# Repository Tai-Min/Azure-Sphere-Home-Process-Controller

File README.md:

# Azure Sphere Home Process Controller
My entry for [Home Is Where the Hack Is Challenge, with Avnet Azure Sphere](https://www.element14.com/community/docs/DOC-94716?CMP=e-email-ADH-e14-Com-170420-Avnet-2391) (Grand Prize winner!)

Industrial like PID / Two state process controller with web based configuration, MQTT communication and Azure IoT Central integration.

This repository contains source code for both High level application and real time core of Azure Sphere board, source codes for Arduino expansion cards, electronic design files for KiCad, housing design files for Autodesk Inventor and STL files for 3d printing.

For details how it was created and how to use it click [here](https://www.element14.com/community/groups/azuresphere/blog/2020/05/29/azure-sphere-home-process-controller)

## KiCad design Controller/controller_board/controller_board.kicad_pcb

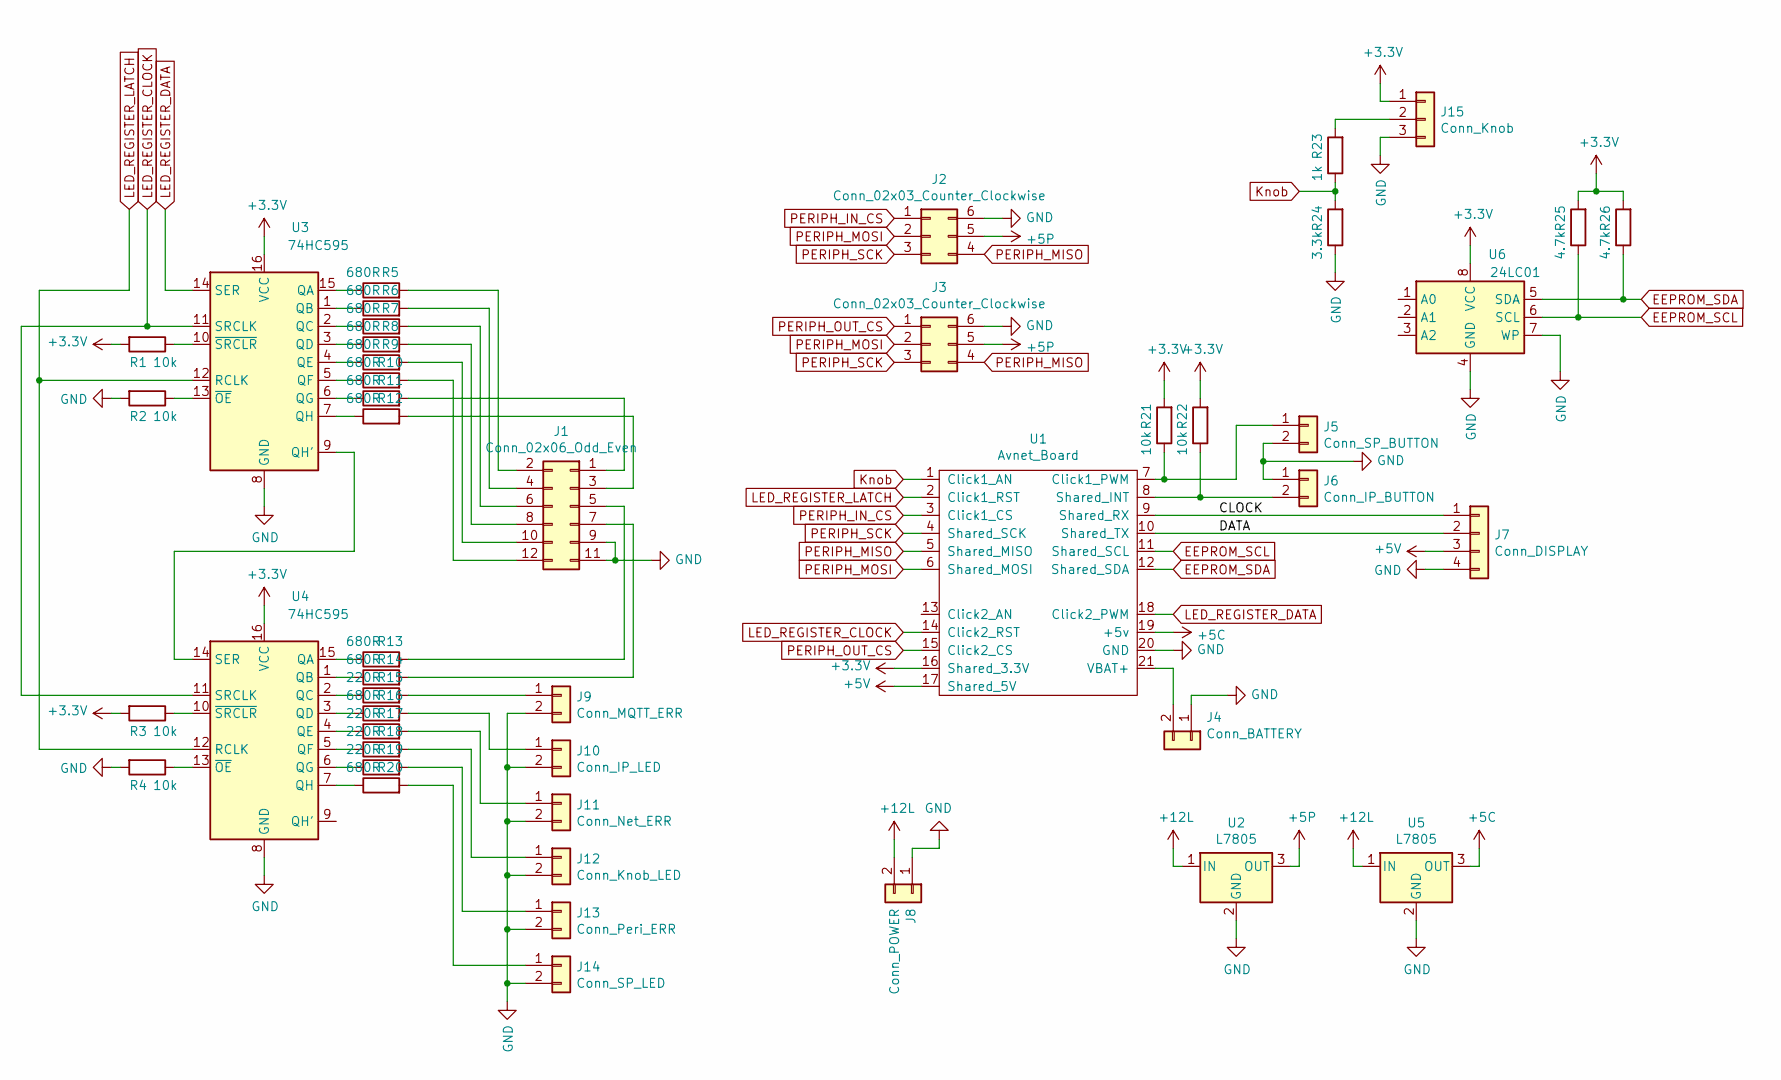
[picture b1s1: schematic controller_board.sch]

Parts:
J1: Conn_02x06_Odd_Even; PinHeader_2x06_P2.54mm_Vertical
J2: Conn_02x03_Counter_Clockwise; PinSocket_2x03_P2.54mm_Horizontal
J3: Conn_02x03_Counter_Clockwise; PinHeader_2x03_P2.54mm_Horizontal
J4: Conn_BATTERY; PinHeader_1x02_P2.54mm_Vertical
J5: Conn_SP_BUTTON; PinHeader_1x02_P2.54mm_Vertical
J6: Conn_IP_BUTTON; PinHeader_1x02_P2.54mm_Vertical
J7: Conn_DISPLAY; PinHeader_1x04_P2.54mm_Vertical
J8: Conn_POWER; PhoenixContact_MSTBA_2,5_2-G_1x02_P5.00mm_Horizontal
J9: Conn_MQTT_ERR; PinHeader_1x02_P2.54mm_Vertical
J10: Conn_IP_LED; PinHeader_1x02_P2.54mm_Vertical
J11: Conn_Net_ERR; PinHeader_1x02_P2.54mm_Vertical
J12: Conn_Knob_LED; PinHeader_1x02_P2.54mm_Vertical
J13: Conn_Peri_ERR; PinHeader_1x02_P2.54mm_Vertical
J14: Conn_SP_LED; PinHeader_1x02_P2.54mm_Vertical
J15: Conn_Knob; PinHeader_1x03_P2.54mm_Vertical
R1, R2, R3, R4, R21, R22: 10k; R_Axial_DIN0207_L6.3mm_D2.5mm_P10.16mm_Horizontal
R5, R6, R7, R8, R9, R10, R11, R12, R13, R14, R16, R20: 680R; R_Axial_DIN0207_L6.3mm_D2.5mm_P10.16mm_Horizontal
R15, R17, R18, R19: 220R; R_Axial_DIN0207_L6.3mm_D2.5mm_P10.16mm_Horizontal
R23: 1k; R_Axial_DIN0207_L6.3mm_D2.5mm_P10.16mm_Horizontal
R24: 3.3k; R_Axial_DIN0207_L6.3mm_D2.5mm_P10.16mm_Horizontal
R25, R26: 4.7k; R_Axial_DIN0207_L6.3mm_D2.5mm_P10.16mm_Horizontal
U1: Avnet_Board; Avnet_Azure_Sphere
U2, U5: L7805; TO-220-3_Vertical
U3, U4: 74HC595; DIP-16_W7.62mm_LongPads
U6: 24LC01; DIP-8_W7.62mm_LongPads

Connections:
+3V3: J15.1, R1.2, R3.2, R21.2, R22.2, R25.2, R26.2, U1.16 (Shared_3.3V), U3.16 (VCC), U4.16 (VCC), U6.8 (VCC)
+5C: U1.19 (+5v), U5.3 (OUT)
+5P: J2.5, J3.5, U2.3 (OUT)
+5V: J7.3, U1.17 (Shared_5V)
+12L: J8.2, U2.1 (IN), U5.1 (IN)
/CLOCK: J7.1, U1.9 (Shared_RX)
/DATA: J7.2, U1.10 (Shared_TX)
EEPROM_SCL: R25.1, U1.11 (Shared_SCL), U6.6 (SCL)
EEPROM_SDA: R26.1, U1.12 (Shared_SDA), U6.5 (SDA)
GND: J1.9, J1.11, J2.6, J3.6, J4.1, J5.2, J6.1, J7.4, J8.1, J9.2, J10.2, J11.2, J12.2, J13.2, J14.2, J15.3, R2.2, R4.2, R24.1, U1.20 (GND), U2.2 (GND), U3.8 (GND), U4.8 (GND), U5.2 (GND), U6.4 (GND), U6.7 (WP)
Knob: R23.1, R24.2, U1.1 (Click1_AN)
LED_REGISTER_CLOCK: U1.14 (Click2_RST), U3.11 (SRCLK), U4.11 (SRCLK)
LED_REGISTER_DATA: U1.18 (Click2_PWM), U3.14 (SER)
LED_REGISTER_LATCH: U1.2 (Click1_RST), U3.12 (RCLK), U4.12 (RCLK)
unnamed: J1.1, R11.2
unnamed: J1.2, R5.2
unnamed: J1.3, R12.2
unnamed: J1.4, R6.2
unnamed: J1.5, R13.2
unnamed: J1.6, R7.2
unnamed: J1.7, R14.2
unnamed: J1.8, R8.2
unnamed: J1.10, R9.2
unnamed: J1.12, R10.2
unnamed: J4.2, U1.21 (VBAT+)
unnamed: J5.1, R21.1, U1.7 (Click1_PWM)
unnamed: J6.2, R22.1, U1.8 (Shared_INT)
unnamed: J9.1, R15.2
unnamed: J10.1, R16.2
unnamed: J11.1, R17.2
unnamed: J12.1, R18.2
unnamed: J13.1, R19.2
unnamed: J14.1, R20.2
unnamed: J15.2, R23.2
unnamed: R1.1, U3.10 (~SRCLR)
unnamed: R2.1, U3.13 (~OE)
unnamed: R3.1, U4.10 (~SRCLR)
unnamed: R4.1, U4.13 (~OE)
unnamed: R5.1, U3.15 (QA)
unnamed: R6.1, U3.1 (QB)
unnamed: R7.1, U3.2 (QC)
unnamed: R8.1, U3.3 (QD)
unnamed: R9.1, U3.4 (QE)
unnamed: R10.1, U3.5 (QF)
unnamed: R11.1, U3.6 (QG)
unnamed: R12.1, U3.7 (QH)
unnamed: R13.1, U4.15 (QA)
unnamed: R14.1, U4.1 (QB)
unnamed: R15.1, U4.2 (QC)
unnamed: R16.1, U4.3 (QD)
unnamed: R17.1, U4.4 (QE)
unnamed: R18.1, U4.5 (QF)
unnamed: R19.1, U4.6 (QG)
unnamed: R20.1, U4.7 (QH)
unnamed: U3.9 (QH'), U4.14 (SER)
PERIPH_IN_CS: J2.1, U1.3 (Click1_CS)
PERIPH_MISO: J2.4, J3.4, U1.5 (Shared_MISO)
PERIPH_MOSI: J2.2, J3.2, U1.6 (Shared_MOSI)
PERIPH_OUT_CS: J3.1, U1.15 (Click2_CS)
PERIPH_SCK: J2.3, J3.3, U1.4 (Shared_SCK)

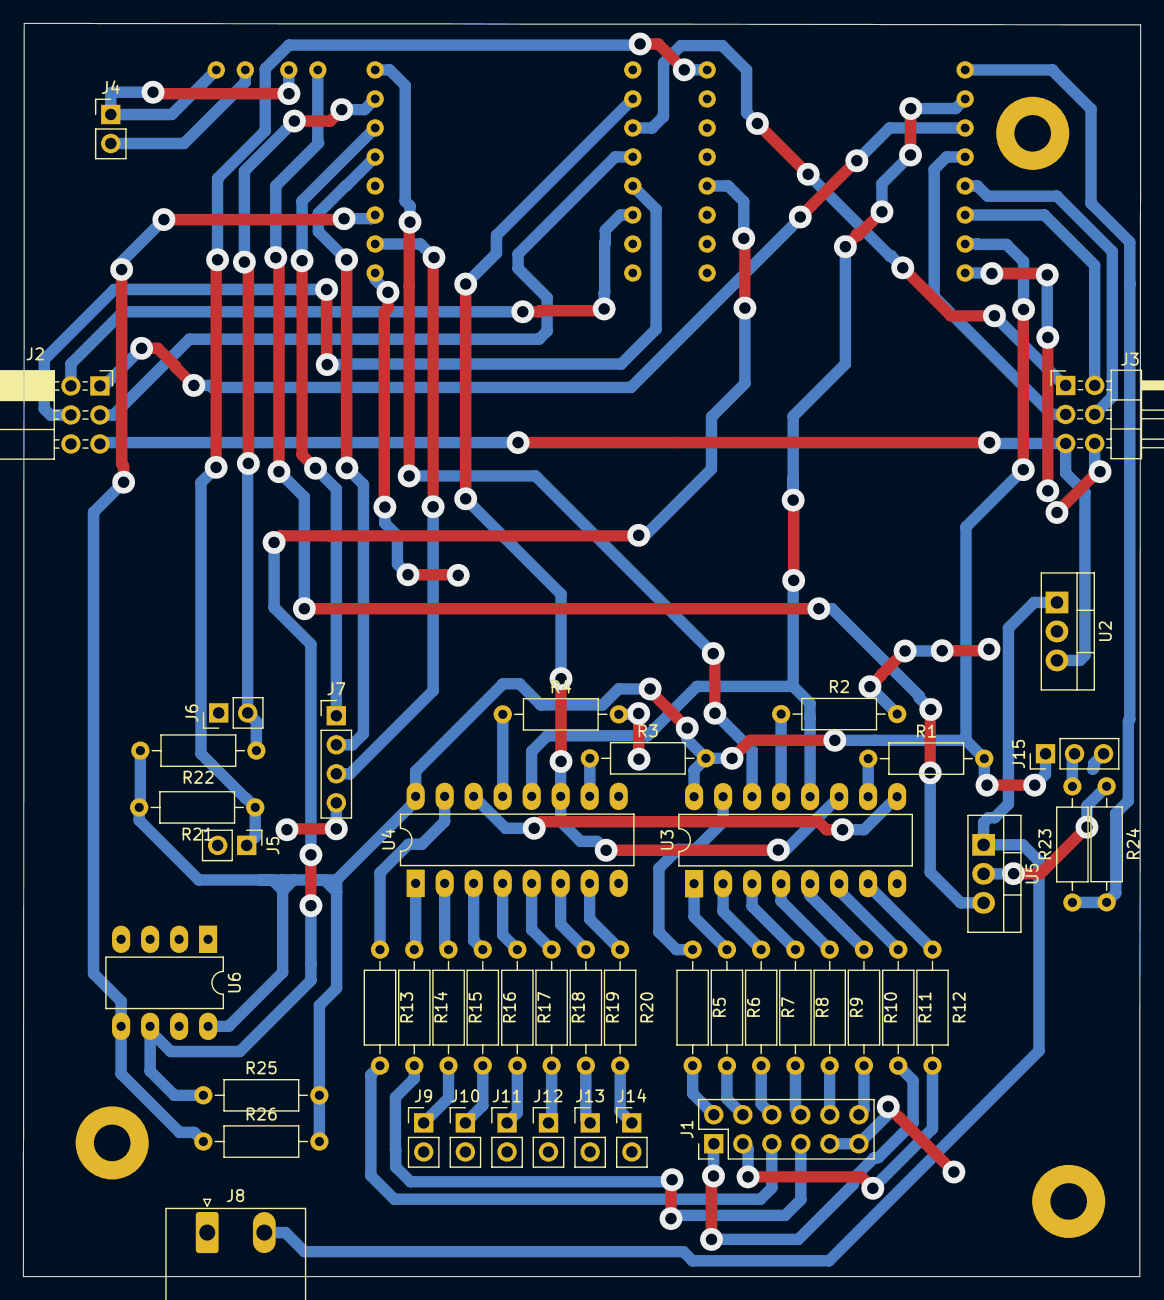
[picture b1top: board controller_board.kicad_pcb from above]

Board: 2 copper layers, 97.8 x 109.7 mm, 50 parts (1 on the bottom side), 60 nets.

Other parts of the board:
 : MountingHole_3.2mm_M3_Pad
  : MountingHole_3.2mm_M3_Pad
 #2: MountingHole_3.2mm_M3_Pad

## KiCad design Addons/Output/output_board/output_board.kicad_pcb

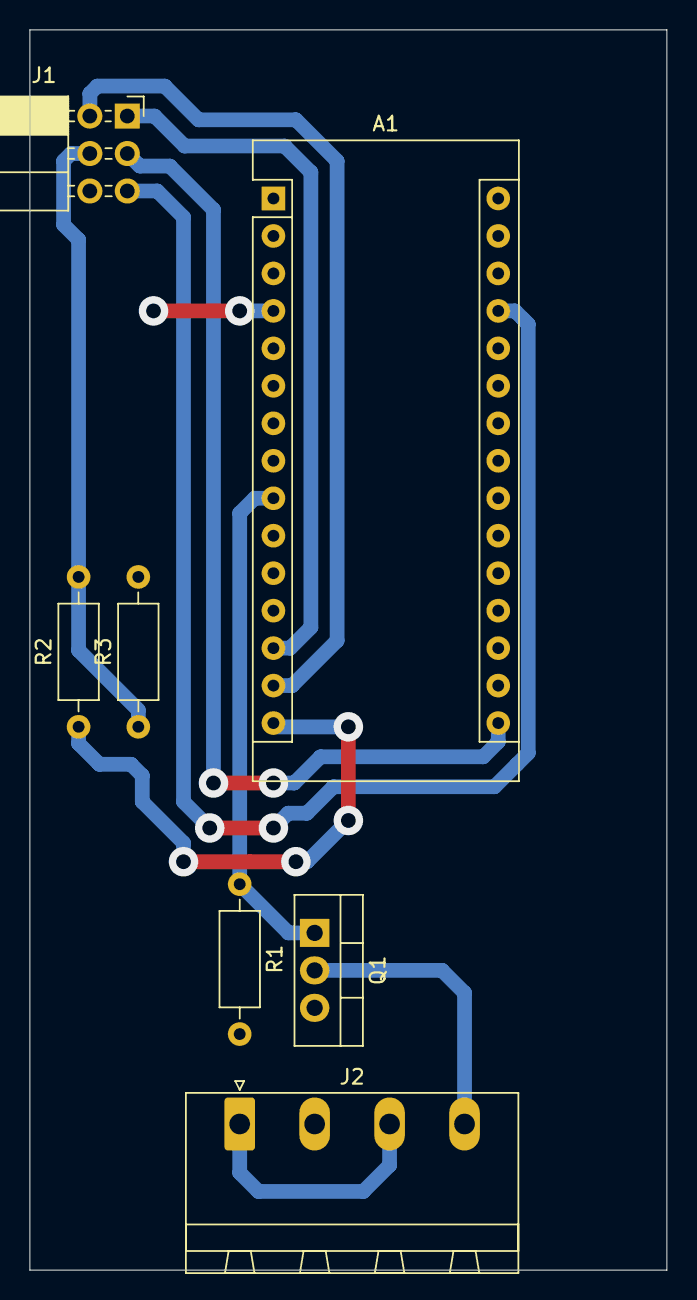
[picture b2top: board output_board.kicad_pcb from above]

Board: 2 copper layers, 43.2 x 84.1 mm, 7 parts (0 on the bottom side), 10 nets.

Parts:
A1: Arduino_Nano_v2.x; Arduino_Nano
J1: Conn_02x03_Odd_Even; PinSocket_2x03_P2.54mm_Horizontal
J2: Conn_01x04; PhoenixContact_MSTBA_2,5_4-G-5,08_1x04_P5.08mm_Horizontal
Q1: BSP129; TO-220-3_Vertical
R1, R2, R3: R; R_Axial_DIN0207_L6.3mm_D2.5mm_P10.16mm_Horizontal

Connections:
+5V: A1.27, J1.5
+12V: J2.1, J2.3
CS: A1.13, J1.1
GND: A1.4, A1.29, J1.6, J2.2, Q1.3, R1.2, R3.2
MISO: J1.4, R2.2, R3.1
MOSI: A1.14, J1.2
unnamed: A1.9, Q1.1, R1.1
unnamed: A1.15, R2.1
unnamed: J2.4, Q1.2
SCK: A1.16, J1.3

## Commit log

2020-05-15 Global cleanup, add EEPROM
2020-05-23 comment all the stuff, fix memory leaks
2020-05-29 add stl files
2020-05-29 Create LICENSE
2020-05-31 fix app manifest
2020-06-11 Fix doxygen syntax
2020-06-11 Add proper README
